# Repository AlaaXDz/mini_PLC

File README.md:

# mini_PLC
A mini PLC based on Arduino nano

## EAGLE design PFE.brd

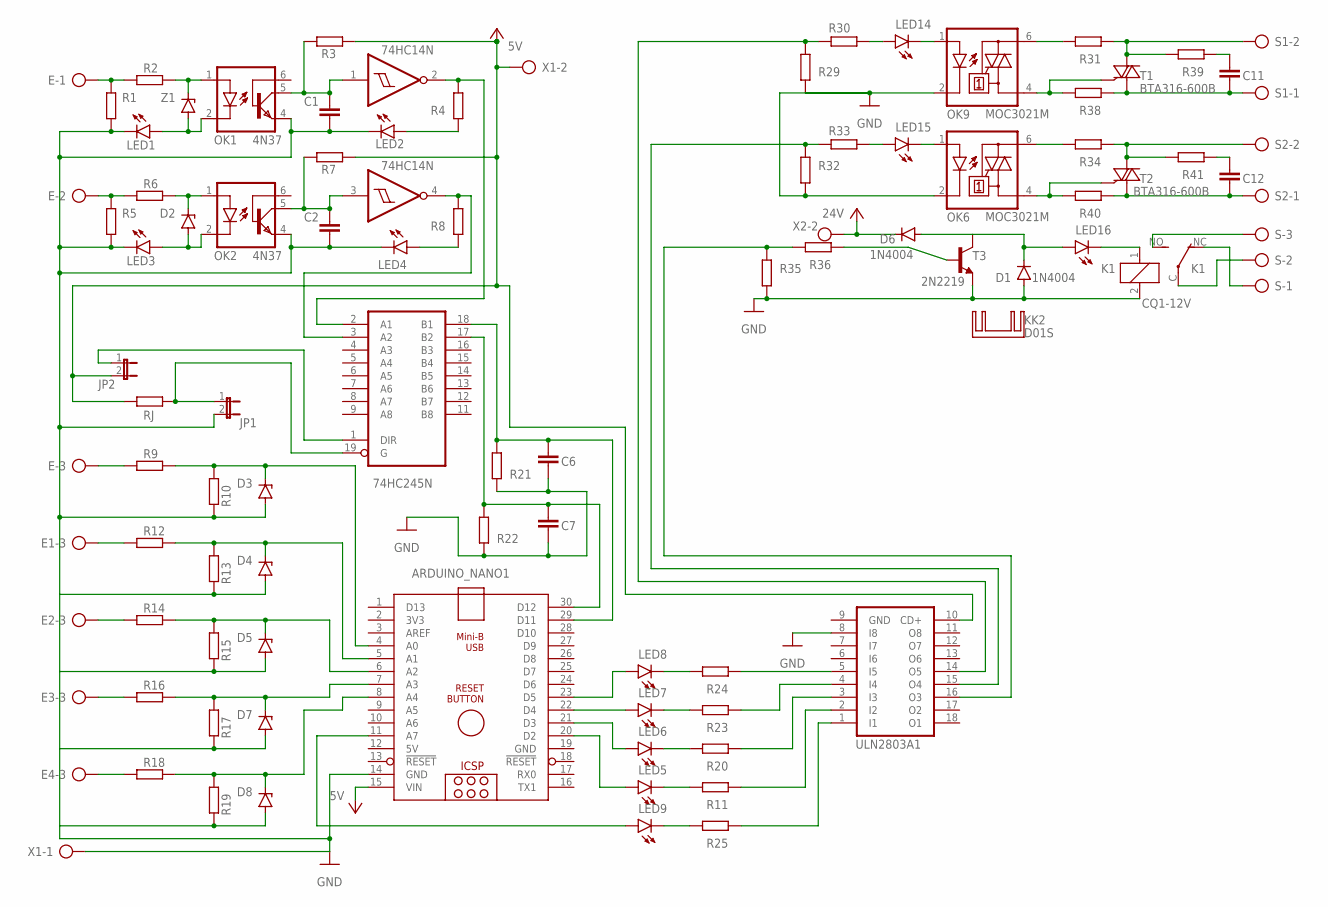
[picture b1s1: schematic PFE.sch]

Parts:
ARDUINO_NANO1: ARDUINO_NANO
C1, C2, C6, C7, C11, C12: C-EU075-052X106; C075-052X106
D1, D6: 1N4004; DO41-10
D2, D3, D4, D5, D7, D8: 1N4728; DO41Z10
E, E1, E2, E3, E4: AK300/5
IC1: 74HC14N; DIL14
IC2: 74HC245N; DIL20
JP1, JP2: JP1E; JP1
K1: CQ1-12V; CQ1
KK2: D01S
LED1, LED2, LED3, LED4, LED5, LED6, LED7, LED8, LED9, LED14, LED15, LED16: TLLY4400; LED3MM
OK1, OK2: 4N37; DIL06
OK6, OK9: MOC3021M; DIL06
R1, R2, R3, R4, R5, R6, R7, R8, R9, R10, R11, R12, R13, R14, R15, R16, R17, R18, R19, R20, R21, R22, R23, R24, R25, R29, R30, R31, R32, R33, R34, R35, R36, R38, R39, R40, R41: R-EU_0204/7; 0204/7
RJ: R-EU_0204/7; 0204/7
S: AK300/3
S1, S2: AK300/2
T1, T2: BTA316-600B; SOT78A
T3: 2N2219; TO5
ULN2803A1: ULN2803A; DIL18
X1, X2: AK300/2
Z1: 1N4728; DO41Z10

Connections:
5V: ARDUINO_NANO1.12 (5V)
GND: ARDUINO_NANO1.14 (GND), ARDUINO_NANO1.19 (GND), C1.2, C2.2, C6.2, C7.2, D1.A, D3.A, IC1.7 (GND), IC2.10 (GND), JP1.2, K1.2, LED1.K (C), LED2.K (C), LED3.K (C), LED4.K (C), OK1.4 (EMI), OK2.4 (EMI), OK6.2 (C), OK9.2 (C), R1.1, R5.1, R10.2, R21.2, R22.2, R29.1, R32.1, R35.1, T3.1 (E), ULN2803A1.8 (I8), ULN2803A1.9 (GND), X1.1
GND1: D4.A, R13.2
GND2: D5.A, R15.2
GND3: D7.A, R17.2
GND4: D8.A, R19.2
unnamed: E.1, R1.2, R2.1
unnamed: D2.A, LED3.A, OK2.2 (C)
unnamed: OK1.1 (A), R2.2, Z1.C
unnamed: C1.1, IC1.1 (I), OK1.5 (COL), R3.1
unnamed: D2.C, OK2.1 (A), R6.2
unnamed: ARDUINO_NANO1.11 (A7), LED9.A
unnamed: E.2, R5.2, R6.1
unnamed: C2.1, IC1.3 (I), OK2.5 (COL), R7.1
unnamed: LED6.K (C), R20.1
unnamed: ARDUINO_NANO1.4 (A0), D3.C, R9.2, R10.1
unnamed: ARDUINO_NANO1.29 (D11), C6.1, IC2.18 (B1), R21.1
unnamed: E.3, R9.1
unnamed: LED4.A, R8.2
unnamed: E1.3, R12.1
unnamed: LED1.A, OK1.2 (C), Z1.A
unnamed: IC1.4 (O), IC2.3 (A2), R8.1
unnamed: ARDUINO_NANO1.6 (A2), D5.C, R14.2, R15.1
unnamed: E2.3, R14.1
unnamed: LED7.K (C), R23.1
unnamed: E3.3, R16.1
unnamed: ARDUINO_NANO1.22 (D4), LED7.A
unnamed: IC2.19 (G), JP1.1, RJ.1
unnamed: LED14.A, R30.2
unnamed: E4.3, R18.1
unnamed: OK6.4 (A1), R40.1, T2.G
unnamed: R32.2, R33.1, ULN2803A1.15 (O4)
unnamed: ARDUINO_NANO1.5 (A1), D4.C, R12.2, R13.1
unnamed: LED2.A, R4.2
unnamed: R25.2, ULN2803A1.1 (I1)
unnamed: ARDUINO_NANO1.7 (A3), D7.C, R16.2, R17.1
unnamed: LED14.K (C), OK9.1 (A)
unnamed: ARDUINO_NANO1.8 (A4), D8.C, R18.2, R19.1
unnamed: LED15.A, R33.2
unnamed: IC2.1 (DIR), JP2.1
unnamed: ARDUINO_NANO1.23 (D5), LED8.A
unnamed: R11.2, ULN2803A1.2 (I2)
unnamed: LED15.K (C), OK6.1 (A)
unnamed: ARDUINO_NANO1.30 (D12), C7.1, IC2.17 (B2), R22.1
unnamed: IC1.2 (O), IC2.2 (A1), R4.1
unnamed: LED5.K (C), R11.1
unnamed: LED8.K (C), R24.1
unnamed: R36.2, T3.2 (B)
unnamed: K1.NO (S), S.3
unnamed: LED9.K (C), R25.1
unnamed: R20.2, ULN2803A1.3 (I3)
unnamed: ARDUINO_NANO1.20 (D2), LED5.A
unnamed: R23.2, ULN2803A1.4 (I4)
unnamed: OK9.4 (A1), R38.1, T1.G
unnamed: R35.2, R36.1, ULN2803A1.16 (O3)
unnamed: D1.C, D6.A, LED16.A, T3.3 (C)
unnamed: OK9.6 (A2), R31.1
unnamed: OK6.6 (A2), R34.1
unnamed: R31.2, R39.1, S1.2, T1.T2 (LD)
unnamed: R29.2, R30.1, ULN2803A1.14 (O5)
unnamed: C11.1, R39.2
unnamed: C12.1, R41.2
unnamed: K1.NC (O), S.1
unnamed: K1.C, S.2
unnamed: C11.2, R38.2, S1.1, T1.T1 (CM)
unnamed: ARDUINO_NANO1.21 (D3), LED6.A
unnamed: R34.2, R41.1, S2.2, T2.T2 (LD)
unnamed: K1.1, LED16.K (C)
unnamed: R24.2, ULN2803A1.5 (I5)
unnamed: C12.2, R40.2, S2.1, T2.T1 (CM)
VCC: ARDUINO_NANO1.15 (VIN), D6.C, IC1.14 (VCC), IC2.20 (VCC), JP2.2, R3.2, R7.2, RJ.2, ULN2803A1.10 (CD+), X1.2, X2.2

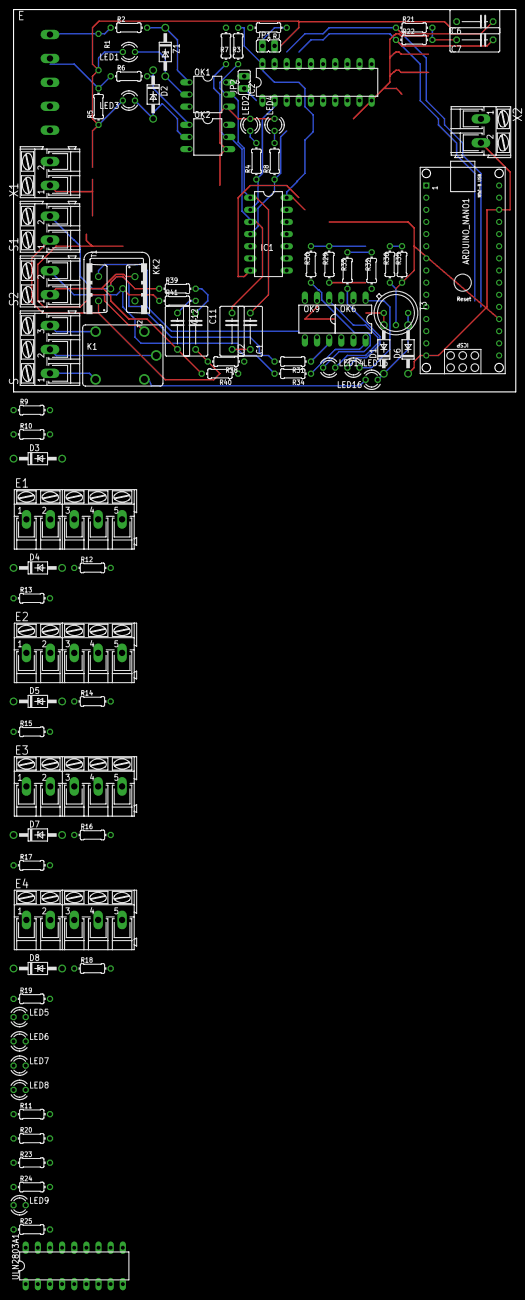
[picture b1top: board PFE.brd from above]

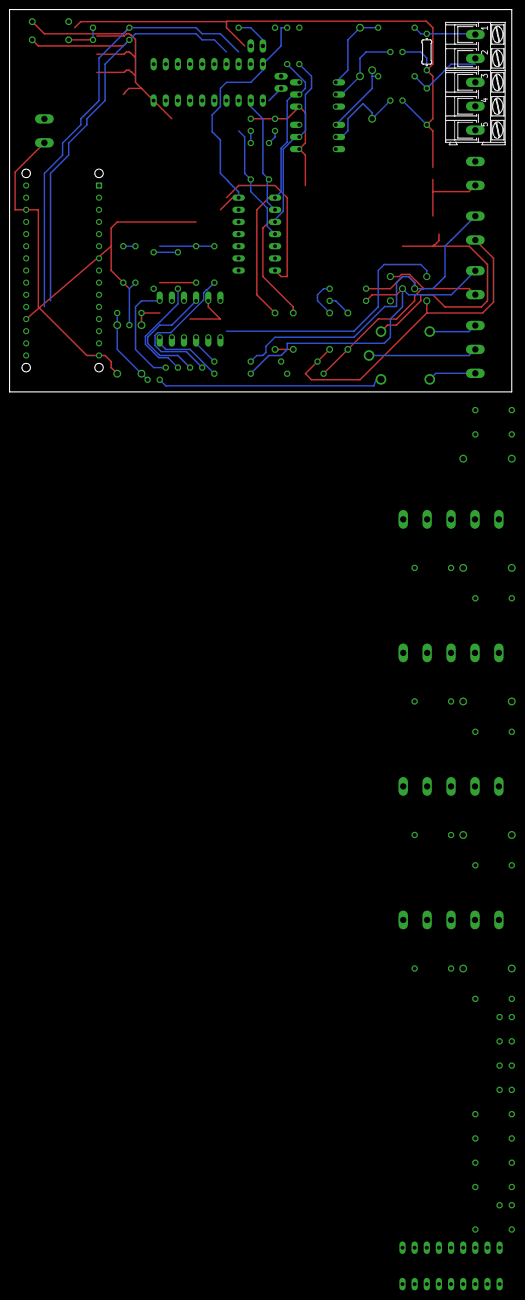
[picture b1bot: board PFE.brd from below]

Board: 2 copper layers, 105.1 x 80.0 mm, 90 parts (2 on the bottom side), 70 nets.

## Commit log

2021-04-14 first essay
2021-04-14 edited the readme file
2021-04-21 added the third triac output
2021-10-25 Create mini_PLC.ino
    Added the Arduino code of the board
